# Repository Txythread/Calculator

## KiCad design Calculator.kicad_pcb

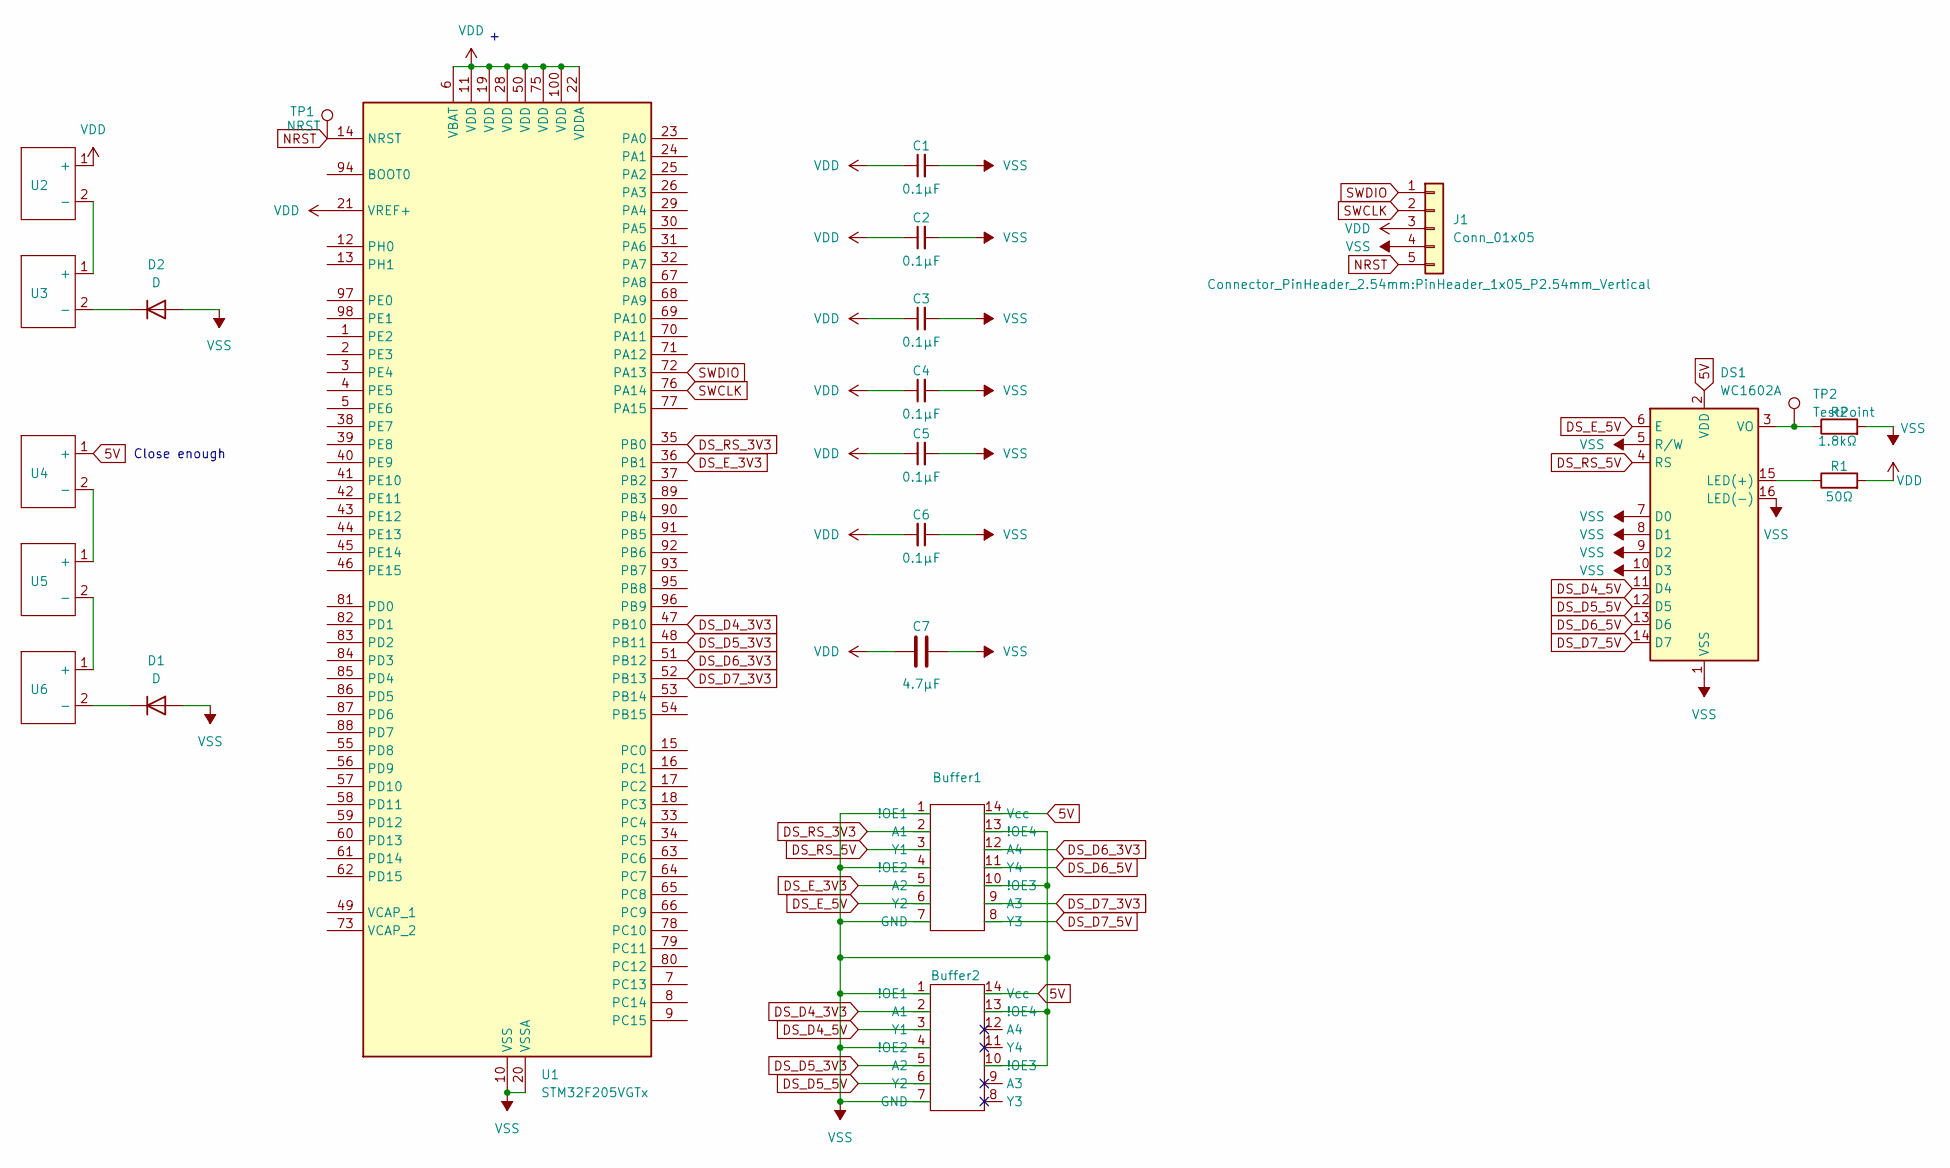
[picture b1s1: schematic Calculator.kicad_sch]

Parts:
Buffer1, Buffer2: SNx4HCT125
C1, C2, C3, C4, C5, C6: 0.1µF; C_0805_2012Metric_Pad1.18x1.45mm_HandSolder
C7: 4.7µF; C_0603_1608Metric_Pad1.08x0.95mm_HandSolder
D1, D2: D; D_DO-35_SOD27_P5.08mm_Vertical_KathodeUp
DS1: WC1602A
J1: Conn_01x05; PinHeader_1x05_P2.54mm_Vertical
R1: 50Ω; R_0805_2012Metric_Pad1.20x1.40mm_HandSolder
R2: 1.8kΩ; R_0603_1608Metric_Pad0.98x0.95mm_HandSolder
TP1: NRST; TestPoint_Pad_D1.0mm
TP2: TestPoint; TestPoint_Pad_D1.0mm
U1: STM32F205VGTx; LQFP-100_14x14mm_P0.5mm
U2, U3, U4, U5, U6: BH-25C-1

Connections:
5V: Buffer1.14 (Vcc), Buffer2.14 (Vcc), DS1.2 (VDD), U4.1 (+)
DS_D4_3V3: Buffer2.2 (A1), U1.47 (PB10)
DS_D4_5V: Buffer2.3 (Y1), DS1.11 (D4)
DS_D5_3V3: Buffer2.5 (A2), U1.48 (PB11)
DS_D5_5V: Buffer2.6 (Y2), DS1.12 (D5)
DS_D6_3V3: Buffer1.12 (A4), U1.51 (PB12)
DS_D6_5V: Buffer1.11 (Y4), DS1.13 (D6)
DS_D7_3V3: Buffer1.9 (A3), U1.52 (PB13)
DS_D7_5V: Buffer1.8 (Y3), DS1.14 (D7)
DS_E_3V3: Buffer1.5 (A2), U1.36 (PB1)
DS_E_5V: Buffer1.6 (Y2), DS1.6 (E)
DS_RS_3V3: Buffer1.2 (A1), U1.35 (PB0)
DS_RS_5V: Buffer1.3 (Y1), DS1.4 (RS)
NRST: J1.5, TP1.1, U1.14 (NRST)
unnamed: D1.1 (K), U6.2 (-)
unnamed: D2.1 (K), U3.2 (-)
unnamed: DS1.15 (LED(+)), R1.1
unnamed: DS1.3 (VO), R2.1, TP2.1
unnamed: U2.2 (-), U3.1 (+)
unnamed: U4.2 (-), U5.1 (+)
unnamed: U5.2 (-), U6.1 (+)
SWCLK: J1.2, U1.76 (PA14)
SWDIO: J1.1, U1.72 (PA13)
VDD: C1.1, C2.1, C3.1, C4.1, C5.1, C6.2, C7.1, J1.3, R1.2, U1.6 (VBAT), U1.11 (VDD), U1.19 (VDD), U1.21 (VREF+), U1.22 (VDDA), U1.28 (VDD), U1.50 (VDD), U1.75 (VDD), U1.100 (VDD), U2.1 (+)
VSS: Buffer1.1 (!OE1), Buffer1.4 (!OE2), Buffer1.7 (GND), Buffer1.10 (!OE3), Buffer1.13 (!OE4), Buffer2.1 (!OE1), Buffer2.4 (!OE2), Buffer2.7 (GND), Buffer2.10 (!OE3), Buffer2.13 (!OE4), C1.2, C2.2, C3.2, C4.2, C5.2, C6.1, C7.2, D1.2 (A), D2.2 (A), DS1.1 (VSS), DS1.5 (R/W), DS1.7 (D0), DS1.8 (D1), DS1.9 (D2), DS1.10 (D3), DS1.16 (LED(-)), J1.4, R2.2, U1.10 (VSS), U1.20 (VSSA), U1.27 (VSS), U1.74 (VSS)

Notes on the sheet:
Close enough

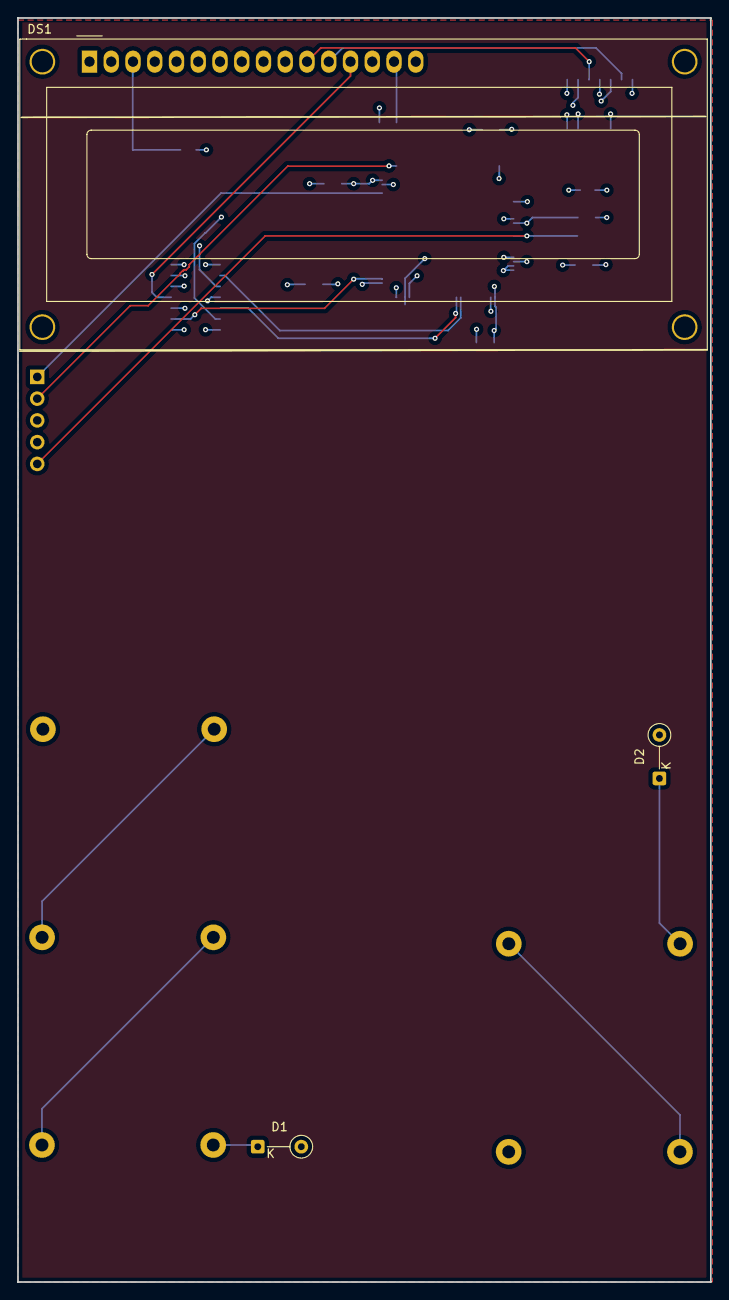
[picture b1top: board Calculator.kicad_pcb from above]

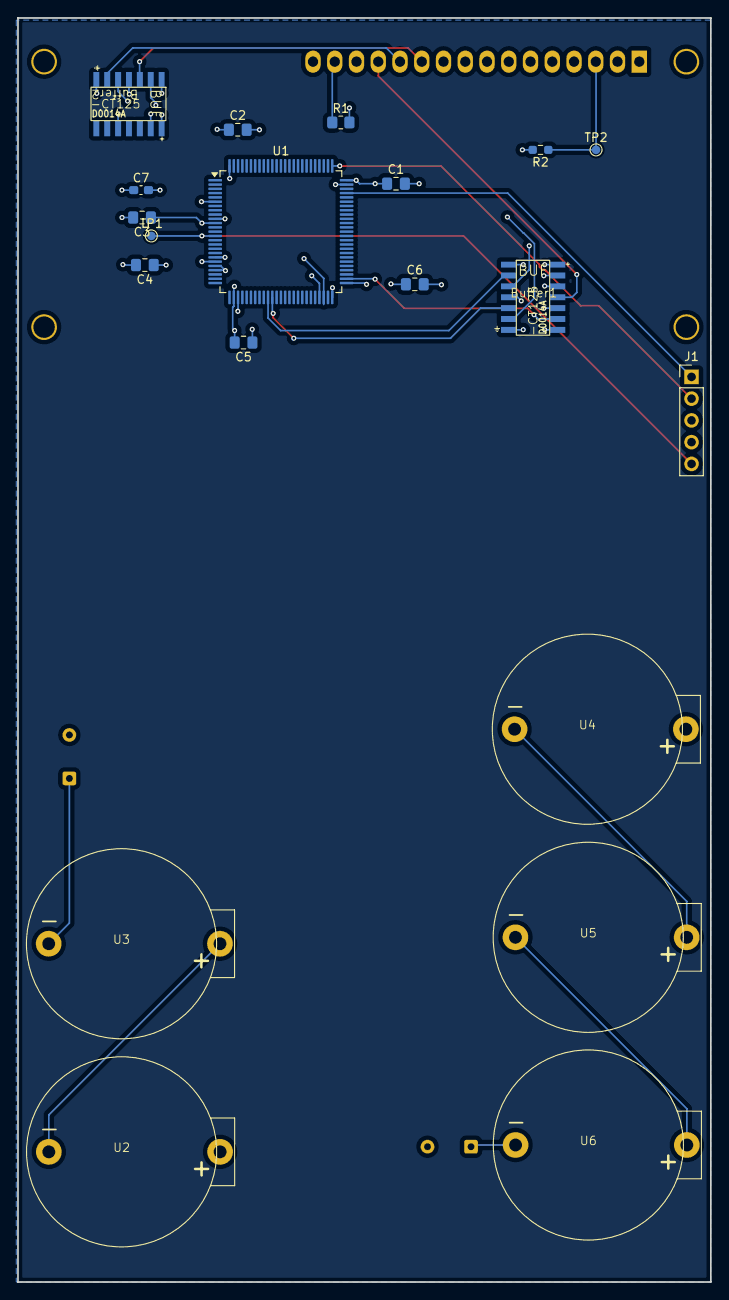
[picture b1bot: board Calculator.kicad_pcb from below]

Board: 6 copper layers, 80.9 x 147.6 mm, 23 parts (20 on the bottom side), 25 nets.

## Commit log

2025-12-06 Added MCU & Decoupling Caps
2025-12-06 Added .gitignore
2025-12-06 Added SWL
2025-12-08 Added Display and Batteries
